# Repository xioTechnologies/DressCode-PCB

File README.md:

DressCode-PCB
=============

A sewable circuit for making LEDs respond to music.  [Firmware](https://github.com/xioTechnologies/DressCode-Firmware) source files are available on GitHub.  See [original post](http://www.x-io.co.uk/dresscode/) for more information.

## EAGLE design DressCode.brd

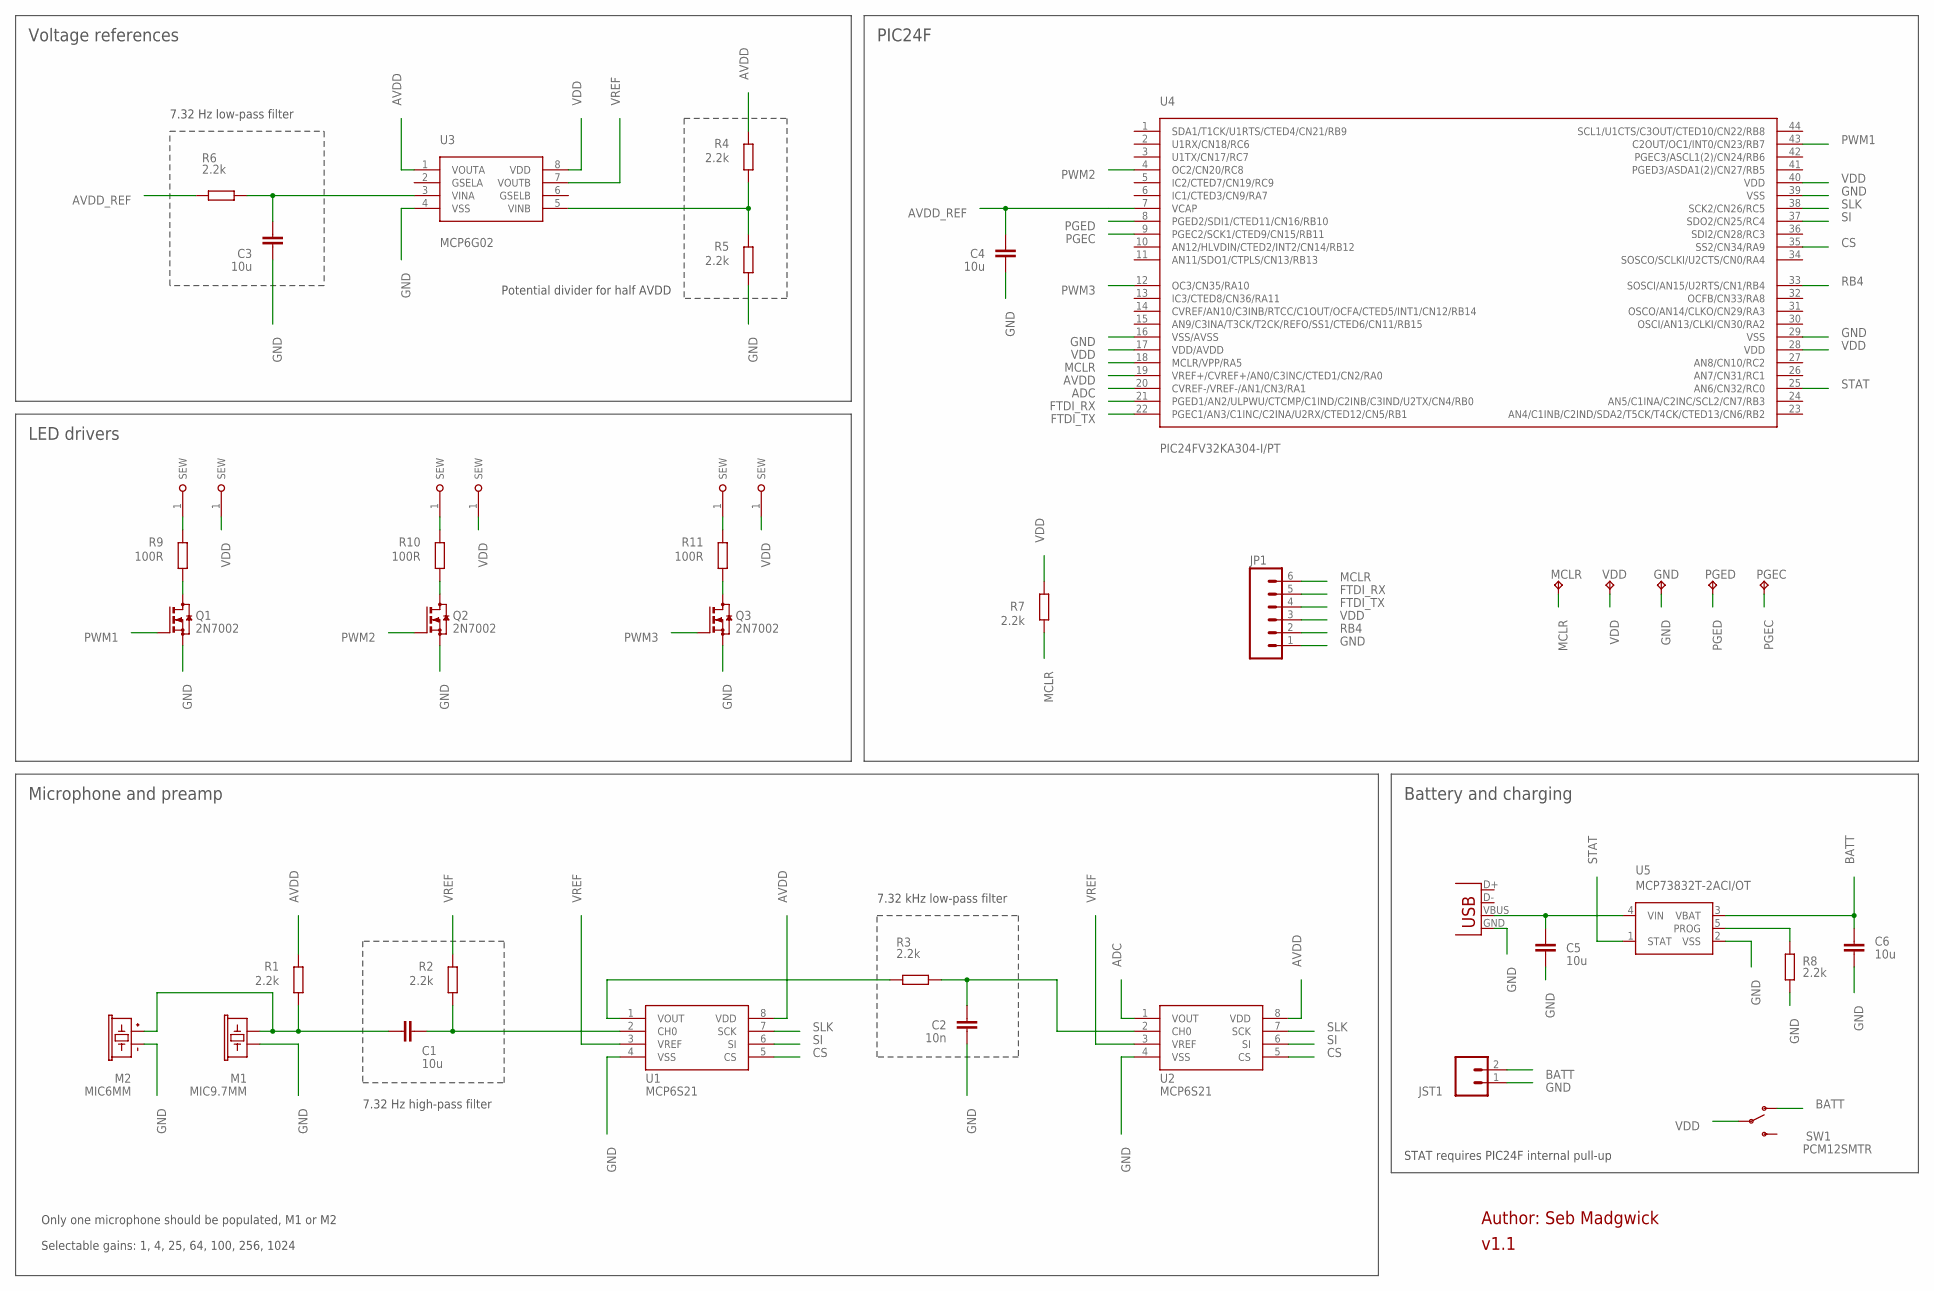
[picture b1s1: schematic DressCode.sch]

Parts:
C1, C3, C4, C5, C6: 10u; C0805
C2: 10n; C0805
GND: TPTP16R; TP16R
JP1: M06SIP; 1X06
JST1: M02-JST-2MM-SMT; JST-2-SMD
M1: MIC9.7MM; MIC-9.7MM
M2: MIC6MM; MIC-SMD
MCLR: TPTP16R; TP16R
PGEC: TPTP16R; TP16R
PGED: TPTP16R; TP16R
Q1, Q2, Q3: 2N7002; SOT23
R1, R2, R3, R4, R5, R6, R7, R8: 2.2k; R0805
R9, R10, R11: 100R; R0805
SW1: PCM12SMTR
U1, U2: MCP6S21; SOIC-8
U3: MCP6G02; SOIC-8
U4: PIC24FV32KA304-I/PT; TQFP44
U5: MCP73832T-2ACI/OT; SOT23-5
U$4, U$5, U$6: DRESSCODE_SEW_PADC; DRESSCODE_SEW_PAD_CIRC
U$7, U$8, U$10: DRESSCODE_SEW_PADS; DRESSCODE_SEW_PAD_SQR
USB1: USB-MICROB
VDD: TPTP16R; TP16R

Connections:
ADC: U2.1 (VOUT), U4.20 (CVREF-/VREF-/AN1/CN3/RA1)
AVDD: R1.2, R4.2, U1.8 (VDD), U2.8 (VDD), U3.1 (VOUTA), U4.19 (VREF+/CVREF+/AN0/C3INC/CTED1/CN2/RA0)
AVDD_REF: C4.2, R6.1, U4.7 (VCAP)
BATT: C6.2, JST1.2, SW1.1 (O), U5.3 (VBAT)
CS: U1.5 (CS), U2.5 (CS), U4.35 (SS2/CN34/RA9)
FTDI_RX: JP1.5, U4.21 (PGED1/AN2/ULPWU/CTCMP/C1IND/C2INB/C3IND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)
FTDI_TX: JP1.4, U4.22 (PGEC1/AN3/C1INC/C2INA/U2RX/CTED12/CN5/R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)
GND: C2.2, C3.1, C4.1, C5.1, C6.1, GND.TP, JP1.1, JST1.1, M1.2, M2.-, Q1.2 (S), Q2.2 (S), Q3.2 (S), R5.1, R8.1, U1.4 (VSS), U2.4 (VSS), U3.4 (VSS), U4.16 (VSS/AVSS), U4.29 (VSS), U4.39 (VSS), U5.2 (VSS), USB1.GND
MCLR: JP1.6, MCLR.TP, R7.1, U4.18 (MCLR/VPP/RA5)
unnamed: C1.1, M1.1, M2.+, R1.1
unnamed: C1.2, R2.1, U1.2 (CH0)
unnamed: C2.1, R3.2, U2.2 (CH0)
unnamed: R3.1, U1.1 (VOUT)
unnamed: C3.2, R6.2, U3.3 (VINA)
unnamed: R4.1, R5.2, U3.5 (VINB)
unnamed: Q1.3 (D), R9.1
unnamed: Q2.3 (D), R10.1
unnamed: Q3.3 (D), R11.1
unnamed: R9.2, U$7.1
unnamed: R10.2, U$8.1
unnamed: R11.2, U$10.1
unnamed: R8.2, U5.5 (PROG)
PGEC: PGEC.TP, U4.9 (PGEC2/SCK1/CTED9/CN15/RB11)
PGED: PGED.TP, U4.8 (PGED2/SDI1/CTED11/CN16/RB10)
PWM1: Q1.1 (G), U4.43 (C2OUT/OC1/INT0/CN23/RB7)
PWM2: Q2.1 (G), U4.4 (OC2/CN20/RC8)
PWM3: Q3.1 (G), U4.12 (OC3/CN35/RA10)
RB4: JP1.2, U4.33 (SOSCI/AN15/U2RTS/CN1/RB4)
SI: U1.6 (SI), U2.6 (SI), U4.37 (SDO2/CN25/RC4)
SLK: U1.7 (SCK), U2.7 (SCK), U4.38 (SCK2/CN26/RC5)
STAT: U4.25 (AN6/CN32/RC0), U5.1 (STAT)
USB1: C5.2, U5.4 (VIN), USB1.VBUS
VDD: JP1.3, R7.2, SW1.2, U3.8 (VDD), U4.17 (VDD/AVDD), U4.28 (VDD), U4.40 (VDD), U$4.1, U$5.1, U$6.1, VDD.TP
VREF: R2.2, U1.3 (VREF), U2.3 (VREF), U3.7 (VOUTB)

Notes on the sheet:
7.32 kHz low-pass filter
7.32 Hz high-pass filter
Microphone and preamp
Selectable gains: 1, 4, 25, 64, 100, 256, 1024
Voltage references
Potential divider for half AVDD
7.32 Hz low-pass filter
LED drivers
PIC24F
Battery and charging
Author: Seb Madgwick
Only one microphone should be populated, M1 or M2
v1.1
STAT requires PIC24F internal pull-up

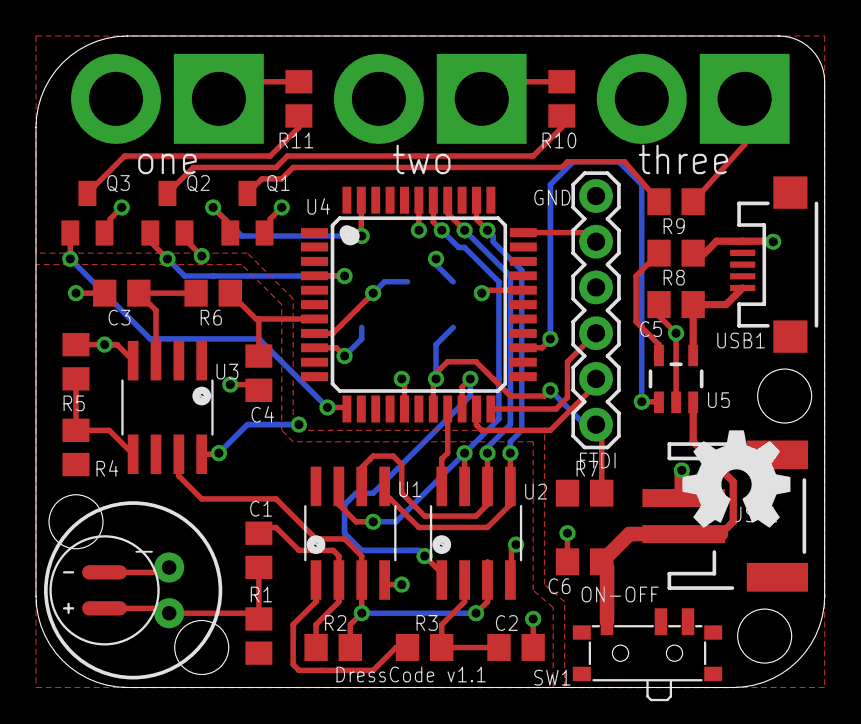
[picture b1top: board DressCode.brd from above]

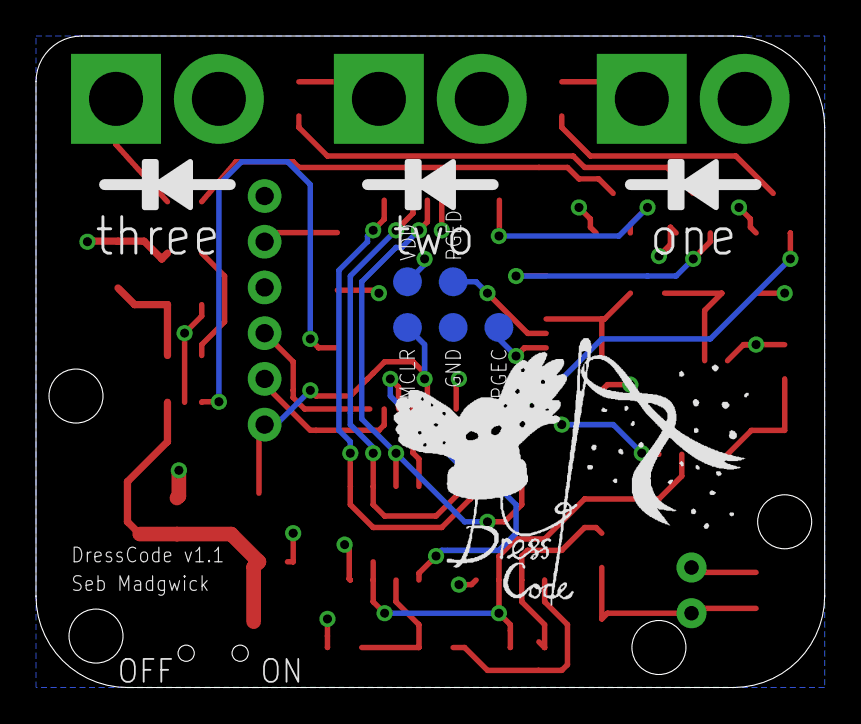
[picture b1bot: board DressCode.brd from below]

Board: 2 copper layers, 43.8 x 36.2 mm, 44 parts (6 on the bottom side), 34 nets.

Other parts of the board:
U$1: OSHW_LOGO_6MM_BOTTOM
U$9: DRESSCODE_LOGO

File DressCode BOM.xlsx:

| Name | Device | Qty | Unit price | Total price
 | R1, R2, R3, R4, R5, R6, R7, R8 | 2.2k, 0805 | 8 | 1.4999999999999999E-2 | 0.12
 | R9, R10, R11 | 100R, 0805 | 3 | 7.0000000000000001E-3 | 2.1000000000000001E-2
 | C1, C3, C4, C5, C6 | 10u, 0805 | 5 | 0.02 | 0.1
 | C2 | 10n, 0805 | 1 | 0.02 | 0.02
 | Q1, Q2, Q3 | 2N7002 (N-channel FET) | 3 | 2.7E-2 | 8.1000000000000003E-2
 | U3 | MCP6G02-E/SN (SGA) | 1 | 0.314 | 0.314
 | U1, U2 | MCP6S21-I/SN (PGA) | 2 | 0.68600000000000005 | 1.3720000000000001
 | M1 | Microphone | 1 | 0.46400000000000002 | 0.46400000000000002
 | M2 | Microphone | 1 | 0.56399999999999995 | 0.56399999999999995
 | U4 | PIC24FV16KA304-I/PT | 1 | 1.91 | 1.91
 | U5 | MCP73832T-2ACI/OT (battery charger) | 1 | 0.38 | 0.38
 | USB1 | Micro USB socket | 1 | 0.51800000000000002 | 0.51800000000000002
 | JST1 | JST battery connector | 1 | 0.49 | 0.49
 | SW1 | Slide switch | 1 | 0.62 | 0.62
 |  |  |  | Total: | 6.9740000000000002
 | Only one microphone should be populated, M1 or M2

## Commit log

2013-04-29 project files added
2013-05-06 JST connector added for LiPo power
2013-05-07 added .MILL file to Gerbers
2013-05-07 design now includes USB charger
2013-05-10 added power switch
2013-05-11 added OSH logo
2013-05-11 irrelevant change to ground polygon
2013-06-20 Add C2 to BOM and USB rework photo
2013-06-20 Fix USB connection error
2013-07-06 Correct link to 10uF capacitor in BOM

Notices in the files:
parts and their libraries:
SparkFun_08_2011: Licensing: CC v3.0 Share-Alike You are welcome to use this library for commercial purposes.
